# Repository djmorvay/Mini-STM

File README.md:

# Mini-STM
Miniature STM32 Personal Project

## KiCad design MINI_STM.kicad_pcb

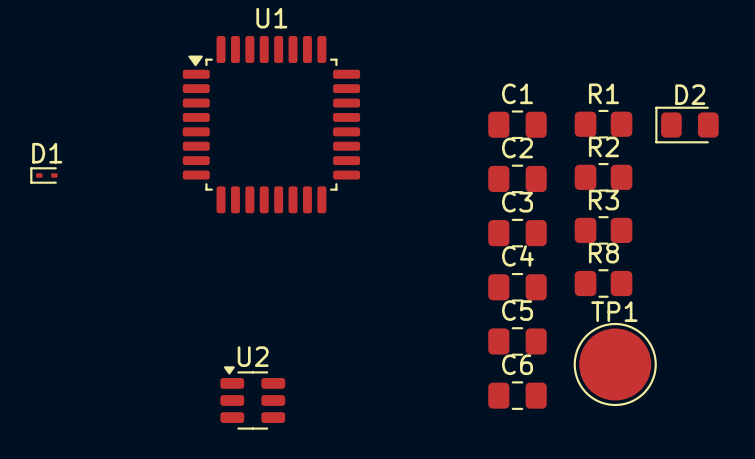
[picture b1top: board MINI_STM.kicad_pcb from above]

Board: 2 copper layers, 15 parts (0 on the bottom side), 9 nets, no tracks yet.

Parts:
C1, C6: 0.1uF; C_0805_2012Metric_Pad1.18x1.45mm_HandSolder
C2, C3: 22uF; C_0805_2012Metric_Pad1.18x1.45mm_HandSolder
C4, C5: 10uF; C_0805_2012Metric_Pad1.18x1.45mm_HandSolder
D1: ESD9B3.3ST5G; D_SOD-923
D2: Green; LED_0805_2012Metric_Pad1.15x1.40mm_HandSolder
R1, R2: 10k; R_0805_2012Metric_Pad1.20x1.40mm_HandSolder
R3: 33.2k; R_0805_2012Metric_Pad1.20x1.40mm_HandSolder
R8: 150R; R_0805_2012Metric_Pad1.20x1.40mm_HandSolder
TP1: +3V3 TP; TestPoint_Pad_D4.0mm
U1: STM32G431KBTx; LQFP-32_7x7mm_P0.8mm
U2: TPS565208; SOT-23-6

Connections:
+3V3: C2.1, C3.1, R3.2, R8.1, TP1.1, U1.1 (VDD), U1.17 (VDD)
/NRST: D1.2 (A2), U1.4 (PG10)
GND: C2.2, C3.2, C4.2, C5.2, C6.2, D1.1 (A1), D2.1 (K), R2.2, U1.14 (VSSA), U1.16 (VSS), U1.32 (VSS), U2.1 (GND)
unnamed: D2.2 (A), R8.2
unnamed: R1.2, U2.5 (EN)
unnamed: C1.2, U2.2 (SW)
unnamed: C1.1, U2.6 (VBST)
unnamed: R2.1, R3.1, U2.4 (VFB)
VIN (+12V): C4.1, C5.1, C6.1, R1.1, U2.3 (VIN)

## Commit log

2024-05-22 First commit.
2024-05-22 Added STM and LDO.
2024-05-22 Changed LDO to buck regulator.
2024-05-22 NRST circuitry added.
2024-05-22 Cleaned up schematic and added programming connector.
2024-05-25 Updates to prgramming connection.
2024-05-26 Added oscillator circuit, but it is not necessary.
2024-05-26 Added more decoupling capacitors and power LED.
2024-05-26 Added more connectors and a power test point.
2024-05-30 Starting PCB layout.
2024-05-31 Adding docs.
